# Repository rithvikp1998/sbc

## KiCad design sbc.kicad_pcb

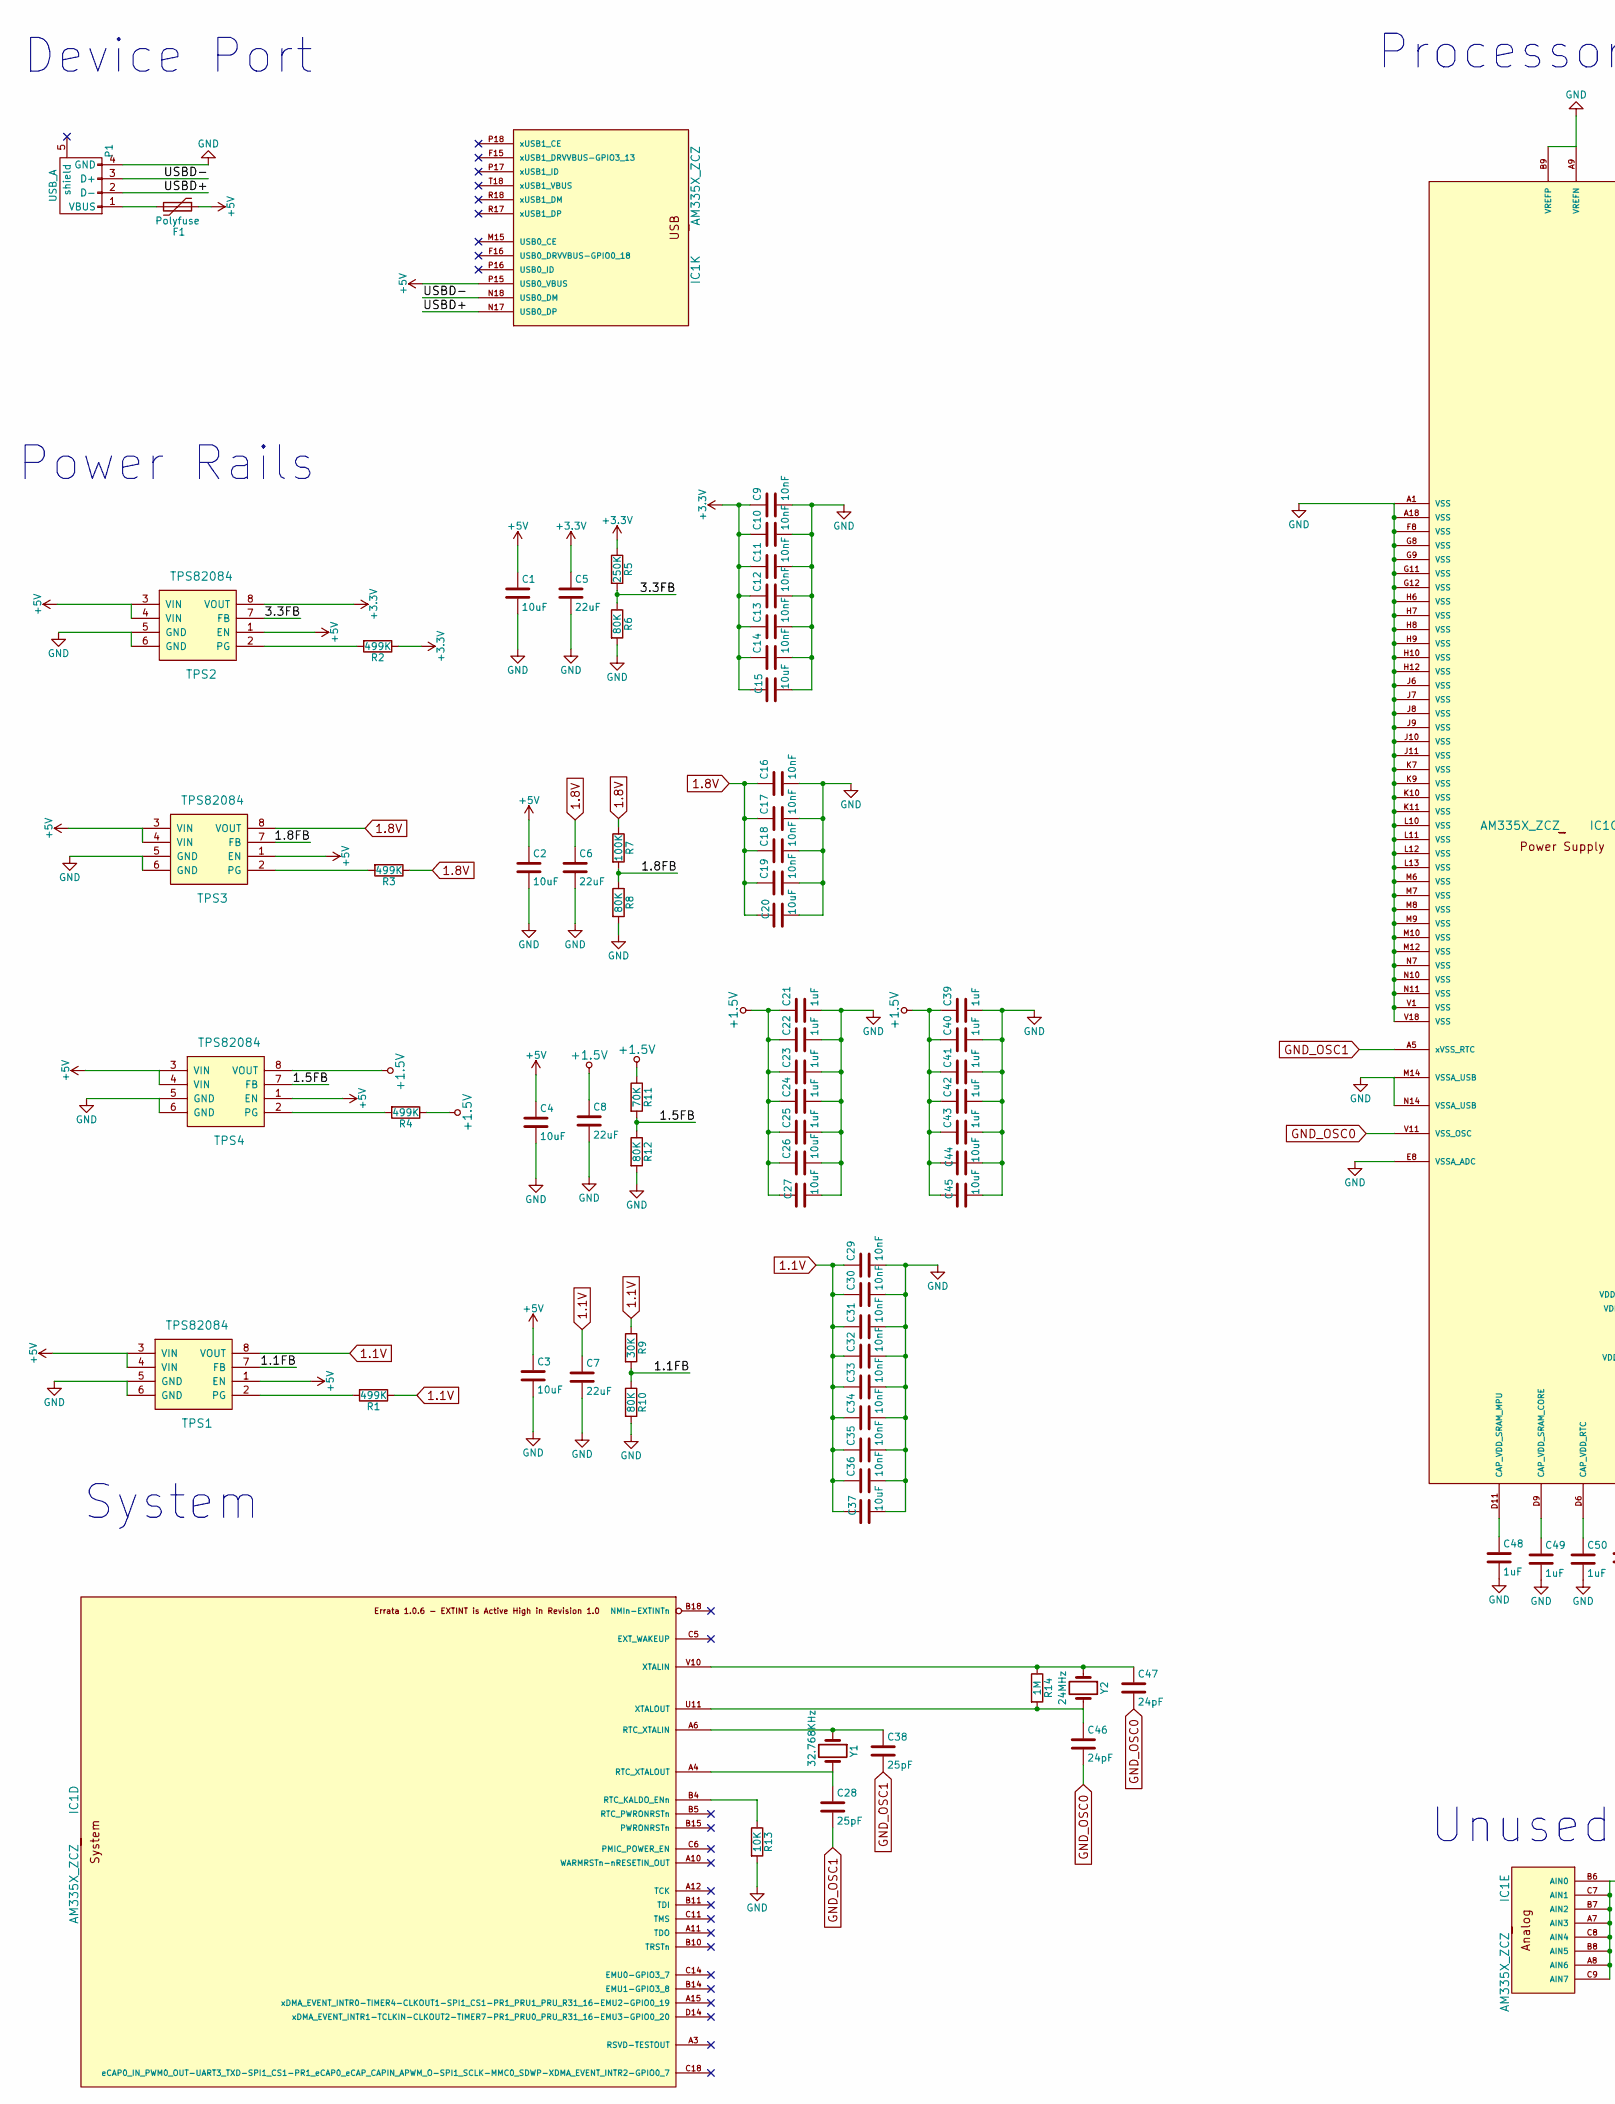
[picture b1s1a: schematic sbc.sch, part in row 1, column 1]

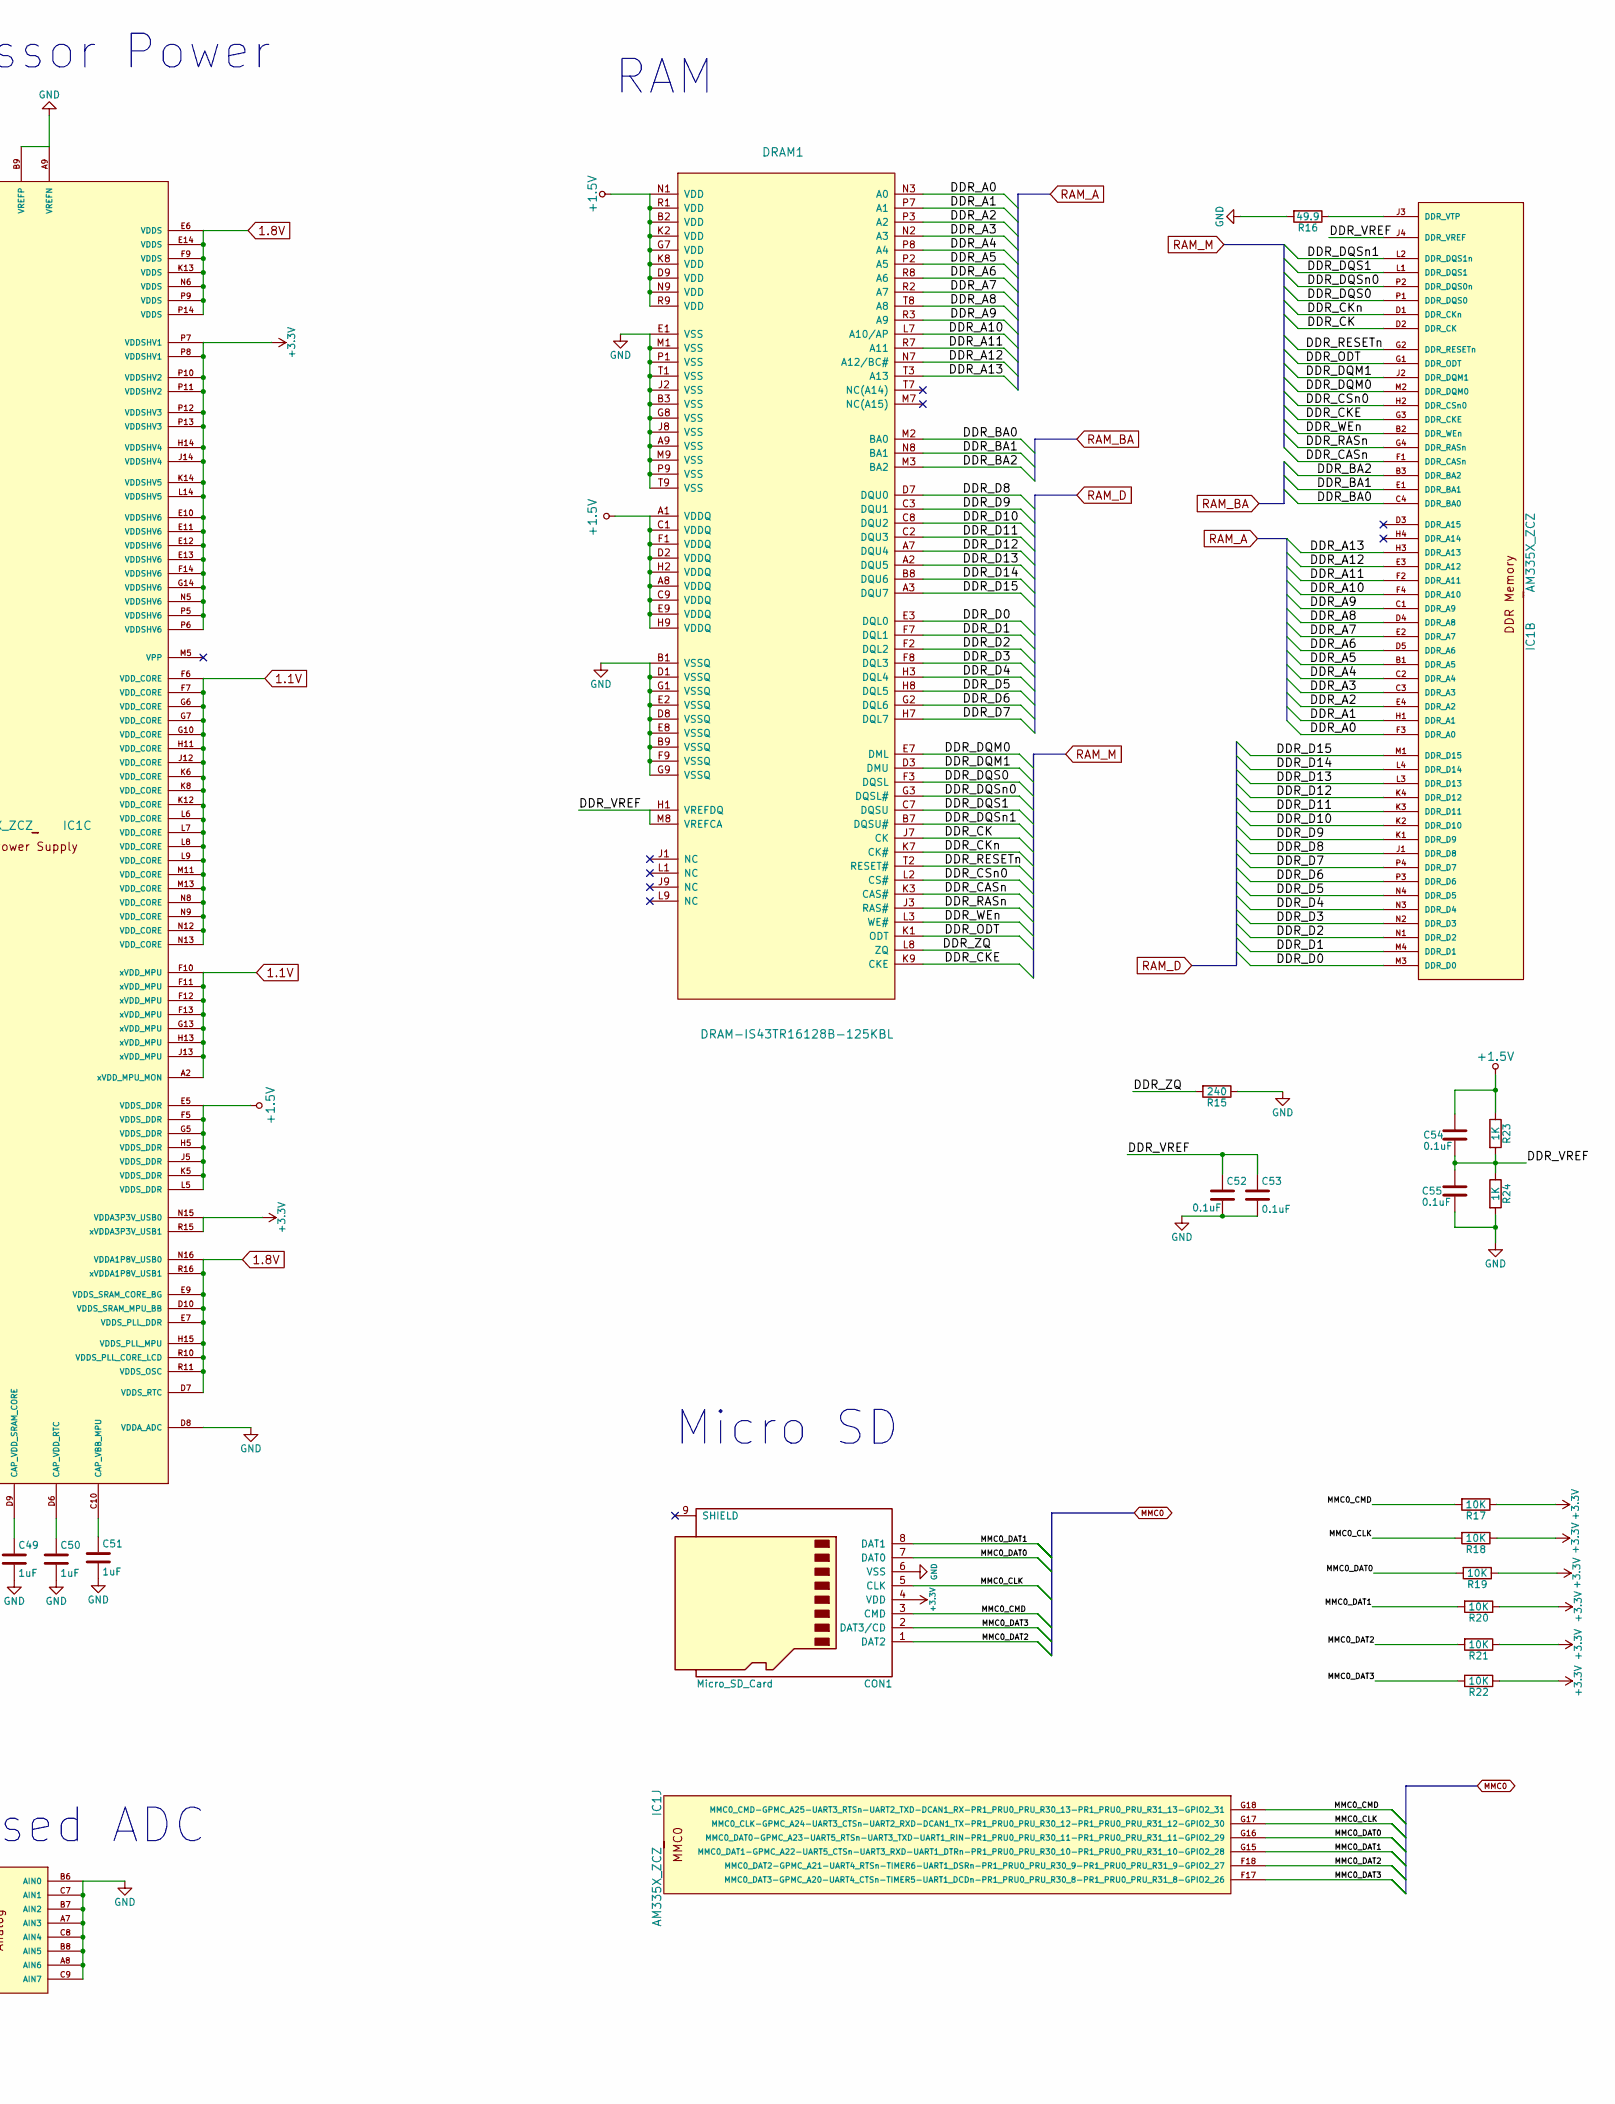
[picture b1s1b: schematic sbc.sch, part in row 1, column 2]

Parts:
C1, C2, C3, C4, C15, C20, C26, C27, C37, C44, C45: 10uF; C_0603_HandSoldering
C5, C6, C7, C8: 22uF; C_0603_HandSoldering
C9, C10, C11, C12, C13, C14, C16, C17, C18, C19, C29, C30, C31, C32, C33, C34, C35, C36: 10nF; C_0603_HandSoldering
C21, C22, C23, C24, C25, C39, C40, C41, C42, C43, C48, C49, C50, C51: 1uF; C_0603_HandSoldering
C28, C38: 25pF; C_0603_HandSoldering
C46, C47: 24pF; C_0603_HandSoldering
C52, C53, C54, C55: 0.1uF; C_0603_HandSoldering
CON1: Micro_SD_Card; MICRO_SD_HINGE_AMP
DRAM1: DRAM-IS43TR16128B-125KBL; BGA-96_pitch0.8mm_dia0.4mm
F1: Polyfuse; Fuse_SMD1206_HandSoldering
IC1: AM335X_ZCZ; bga-csg324
P1: USB_A
R1, R2, R3, R4: 499K; R_0603_HandSoldering
R5: 250K; R_0603_HandSoldering
R6, R8, R10, R12: 80K; R_0603_HandSoldering
R7: 100K; R_0603_HandSoldering
R9: 30K; R_0603_HandSoldering
R11: 70K; R_0603_HandSoldering
R13, R17, R18, R19, R20, R21, R22: 10K; R_0603_HandSoldering
R14: 1M; R_0603_HandSoldering
R15: 240; R_0603_HandSoldering
R16: 49.9; R_0603_HandSoldering
R23, R24: 1K; R_0603_HandSoldering
TPS1, TPS2, TPS3, TPS4: TPS82084; MSOP-8-1EP_3x3mm_Pitch0.65mm
Y1: 32.768KHz; Crystal_SMD_2012-2pin_2.0x1.2mm_HandSoldering
Y2: 24MHz; Crystal_SMD_2012-2pin_2.0x1.2mm_HandSoldering

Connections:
1.1V: C7.1, C29.1, C30.1, C31.1, C32.1, C33.1, C34.1, C35.1, C36.1, C37.2, IC1.A2 (xVDD_MPU_MON), IC1.F6 (VDD_CORE), IC1.F7 (VDD_CORE), IC1.F10 (xVDD_MPU), IC1.F11 (xVDD_MPU), IC1.F12 (xVDD_MPU), IC1.F13 (xVDD_MPU), IC1.G6 (VDD_CORE), IC1.G7 (VDD_CORE), IC1.G10 (VDD_CORE), IC1.G13 (xVDD_MPU), IC1.H11 (VDD_CORE), IC1.H13 (xVDD_MPU), IC1.J12 (VDD_CORE), IC1.J13 (xVDD_MPU), IC1.K6 (VDD_CORE), IC1.K8 (VDD_CORE), IC1.K12 (VDD_CORE), IC1.L6 (VDD_CORE), IC1.L7 (VDD_CORE), IC1.L8 (VDD_CORE), IC1.L9 (VDD_CORE), IC1.M11 (VDD_CORE), IC1.M13 (VDD_CORE), IC1.N8 (VDD_CORE), IC1.N9 (VDD_CORE), IC1.N12 (VDD_CORE), IC1.N13 (VDD_CORE), R1.1, R9.1, TPS1.8 (VOUT)
1.8V: C6.1, C16.1, C17.1, C18.1, C19.1, C20.2, IC1.D7 (VDDS_RTC), IC1.D10 (VDDS_SRAM_MPU_BB), IC1.E6 (VDDS), IC1.E7 (VDDS_PLL_DDR), IC1.E9 (VDDS_SRAM_CORE_BG), IC1.E14 (VDDS), IC1.F9 (VDDS), IC1.H15 (VDDS_PLL_MPU), IC1.K13 (VDDS), IC1.N6 (VDDS), IC1.N16 (VDDA1P8V_USB0), IC1.P9 (VDDS), IC1.P14 (VDDS), IC1.R10 (VDDS_PLL_CORE_LCD), IC1.R11 (VDDS_OSC), IC1.R16 (xVDDA1P8V_USB1), R3.1, R7.1, TPS3.8 (VOUT)
+1.5V: C8.1, C21.1, C22.1, C23.1, C24.1, C25.1, C26.1, C27.2, C39.1, C40.1, C41.1, C42.1, C43.1, C44.2, C45.2, C54.1, DRAM1.A1 (VDDQ), DRAM1.A8 (VDDQ), DRAM1.B2 (VDD), DRAM1.C1 (VDDQ), DRAM1.C9 (VDDQ), DRAM1.D2 (VDDQ), DRAM1.D9 (VDD), DRAM1.E9 (VDDQ), DRAM1.F1 (VDDQ), DRAM1.G7 (VDD), DRAM1.H2 (VDDQ), DRAM1.H9 (VDDQ), DRAM1.K2 (VDD), DRAM1.K8 (VDD), DRAM1.N1 (VDD), DRAM1.N9 (VDD), DRAM1.R1 (VDD), DRAM1.R9 (VDD), IC1.E5 (VDDS_DDR), IC1.F5 (VDDS_DDR), IC1.G5 (VDDS_DDR), IC1.H5 (VDDS_DDR), IC1.J5 (VDDS_DDR), IC1.K5 (VDDS_DDR), IC1.L5 (VDDS_DDR), R4.1, R11.1, R23.1, TPS4.8 (VOUT)
+3V3: C5.1, C9.1, C10.1, C11.1, C12.1, C13.1, C14.1, C15.2, CON1.4 (VDD), IC1.E10 (VDDSHV6), IC1.E11 (VDDSHV6), IC1.E12 (VDDSHV6), IC1.E13 (VDDSHV6), IC1.F14 (VDDSHV6), IC1.G14 (VDDSHV6), IC1.H14 (VDDSHV4), IC1.J14 (VDDSHV4), IC1.K14 (VDDSHV5), IC1.L14 (VDDSHV5), IC1.N5 (VDDSHV6), IC1.N15 (VDDA3P3V_USB0), IC1.P5 (VDDSHV6), IC1.P6 (VDDSHV6), IC1.P7 (VDDSHV1), IC1.P8 (VDDSHV1), IC1.P10 (VDDSHV2), IC1.P11 (VDDSHV2), IC1.P12 (VDDSHV3), IC1.P13 (VDDSHV3), IC1.R15 (xVDDA3P3V_USB1), R2.1, R5.1, R17.1, R18.1, R19.1, R20.1, R21.1, R22.1, TPS2.8 (VOUT)
+5V: C1.1, C2.1, C3.1, C4.1, F1.1, IC1.P15 (USB0_VBUS), TPS1.1 (EN), TPS1.3 (VIN), TPS1.4 (VIN), TPS2.1 (EN), TPS2.3 (VIN), TPS2.4 (VIN), TPS3.1 (EN), TPS3.3 (VIN), TPS3.4 (VIN), TPS4.1 (EN), TPS4.3 (VIN), TPS4.4 (VIN)
/1.1FB: R9.2, R10.1, TPS1.7 (FB)
/1.5FB: R11.2, R12.1, TPS4.7 (FB)
/1.8FB: R7.2, R8.1, TPS3.7 (FB)
/3.3FB: R5.2, R6.1, TPS2.7 (FB)
/DDR_A0: DRAM1.N3 (A0), IC1.F3 (DDR_A0)
/DDR_A1: DRAM1.P7 (A1), IC1.H1 (DDR_A1)
/DDR_A2: DRAM1.P3 (A2), IC1.E4 (DDR_A2)
/DDR_A3: DRAM1.N2 (A3), IC1.C3 (DDR_A3)
/DDR_A4: DRAM1.P8 (A4), IC1.C2 (DDR_A4)
/DDR_A5: DRAM1.P2 (A5), IC1.B1 (DDR_A5)
/DDR_A6: DRAM1.R8 (A6), IC1.D5 (DDR_A6)
/DDR_A7: DRAM1.R2 (A7), IC1.E2 (DDR_A7)
/DDR_A8: DRAM1.T8 (A8), IC1.D4 (DDR_A8)
/DDR_A9: DRAM1.R3 (A9), IC1.C1 (DDR_A9)
/DDR_A10: DRAM1.L7 (A10/AP), IC1.F4 (DDR_A10)
/DDR_A11: DRAM1.R7 (A11), IC1.F2 (DDR_A11)
/DDR_A12: DRAM1.N7 (A12/BC#), IC1.E3 (DDR_A12)
/DDR_A13: DRAM1.T3 (A13), IC1.H3 (DDR_A13)
/DDR_BA0: DRAM1.M2 (BA0), IC1.C4 (DDR_BA0)
/DDR_BA1: DRAM1.N8 (BA1), IC1.E1 (DDR_BA1)
/DDR_BA2: DRAM1.M3 (BA2), IC1.B3 (DDR_BA2)
/DDR_CASn: DRAM1.K3 (CAS#), IC1.F1 (DDR_CASn)
/DDR_CK: DRAM1.J7 (CK), IC1.D2 (DDR_CK)
/DDR_CKE: DRAM1.K9 (CKE), IC1.G3 (DDR_CKE)
/DDR_CKn: DRAM1.K7 (CK#), IC1.D1 (DDR_CKn)
/DDR_CSn0: DRAM1.L2 (CS#), IC1.H2 (DDR_CSn0)
/DDR_D0: DRAM1.E3 (DQL0), IC1.M3 (DDR_D0)
/DDR_D1: DRAM1.F7 (DQL1), IC1.M4 (DDR_D1)
/DDR_D2: DRAM1.F2 (DQL2), IC1.N1 (DDR_D2)
/DDR_D3: DRAM1.F8 (DQL3), IC1.N2 (DDR_D3)
/DDR_D4: DRAM1.H3 (DQL4), IC1.N3 (DDR_D4)
/DDR_D5: DRAM1.H8 (DQL5), IC1.N4 (DDR_D5)
/DDR_D6: DRAM1.G2 (DQL6), IC1.P3 (DDR_D6)
/DDR_D7: DRAM1.H7 (DQL7), IC1.P4 (DDR_D7)
/DDR_D8: DRAM1.D7 (DQU0), IC1.J1 (DDR_D8)
/DDR_D9: DRAM1.C3 (DQU1), IC1.K1 (DDR_D9)
/DDR_D10: DRAM1.C8 (DQU2), IC1.K2 (DDR_D10)
/DDR_D11: DRAM1.C2 (DQU3), IC1.K3 (DDR_D11)
/DDR_D12: DRAM1.A7 (DQU4), IC1.K4 (DDR_D12)
/DDR_D13: DRAM1.A2 (DQU5), IC1.L3 (DDR_D13)
/DDR_D14: DRAM1.B8 (DQU6), IC1.L4 (DDR_D14)
/DDR_D15: DRAM1.A3 (DQU7), IC1.M1 (DDR_D15)
/DDR_DQM0: DRAM1.E7 (DML), IC1.M2 (DDR_DQM0)
/DDR_DQM1: DRAM1.D3 (DMU), IC1.J2 (DDR_DQM1)
/DDR_DQS0: DRAM1.F3 (DQSL), IC1.P1 (DDR_DQS0)
/DDR_DQS1: DRAM1.C7 (DQSU), IC1.L1 (DDR_DQS1)
/DDR_DQSn0: DRAM1.G3 (DQSL#), IC1.P2 (DDR_DQS0n)
/DDR_DQSn1: DRAM1.B7 (DQSU#), IC1.L2 (DDR_DQS1n)
/DDR_ODT: DRAM1.K1 (ODT), IC1.G1 (DDR_ODT)
/DDR_RASn: DRAM1.J3 (RAS#), IC1.G4 (DDR_RASn)
/DDR_RESETn: DRAM1.T2 (RESET#), IC1.G2 (DDR_RESETn)
/DDR_VREF: C52.1, C53.1, C54.2, C55.1, DRAM1.H1 (VREFDQ), DRAM1.M8 (VREFCA), IC1.J4 (DDR_VREF), R23.2, R24.1
/DDR_WEn: DRAM1.L3 (WE#), IC1.B2 (DDR_WEn)
/DDR_ZQ: DRAM1.L8 (ZQ), R15.2
/MMC0_CLK: CON1.5 (CLK), IC1.G17 (MMC0_CLK-GPMC_A24-UART3_CTSn-UART2_RXD-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), R18.2
/MMC0_CMD: CON1.3 (CMD), IC1.G18 (MMC0_CMD-GPMC_A25-UART3_RTSn-UART2_TXD-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), R17.2
/MMC0_DAT0: CON1.7 (DAT0), IC1.G16 (MMC0_DAT0-GPMC_A23-UART5_RTSn-UART3_TXD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), R19.2
/MMC0_DAT1: CON1.8 (DAT1), IC1.G15 (MMC0_DAT1-GPMC_A22-UART5_CTSn-UART3_RXD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), R20.2
/MMC0_DAT2: CON1.1 (DAT2), IC1.F18 (MMC0_DAT2-GPMC_A21-UART4_RTSn-TIMER6-UA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), R21.2
/MMC0_DAT3: CON1.2 (DAT3/CD), IC1.F17 (MMC0_DAT3-GPMC_A20-UART4_CTSn-TIMER5-UA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), R22.2
/USBD+: IC1.N17 (USB0_DP), P1.2 (D-)
/USBD-: IC1.N18 (USB0_DM), P1.3 (D+)
GND: C1.2, C2.2, C3.2, C4.2, C5.2, C6.2, C7.2, C8.2, C9.2, C10.2, C11.2, C12.2, C13.2, C14.2, C15.1, C16.2, C17.2, C18.2, C19.2, C20.1, C21.2, C22.2, C23.2, C24.2, C25.2, C26.2, C27.1, C29.2, C30.2, C31.2, C32.2, C33.2, C34.2, C35.2, C36.2, C37.1, C39.2, C40.2, C41.2, C42.2, C43.2, C44.1, C45.1, C48.2, C49.2, C50.2, C51.2, C52.2, C53.2, C55.2, CON1.6 (VSS), DRAM1.A9 (VSS), DRAM1.B1 (VSSQ), DRAM1.B3 (VSS), DRAM1.B9 (VSSQ), DRAM1.D1 (VSSQ), DRAM1.D8 (VSSQ), DRAM1.E1 (VSS), DRAM1.E2 (VSSQ), DRAM1.E8 (VSSQ), DRAM1.F9 (VSSQ), DRAM1.G1 (VSSQ), DRAM1.G8 (VSS), DRAM1.G9 (VSSQ), DRAM1.J2 (VSS), DRAM1.J8 (VSS), DRAM1.M1 (VSS), DRAM1.M9 (VSS), DRAM1.P1 (VSS), DRAM1.P9 (VSS), DRAM1.T1 (VSS), DRAM1.T9 (VSS), IC1.A1 (VSS), IC1.A7 (AIN3), IC1.A8 (AIN6), IC1.A9 (VREFN), IC1.A18 (VSS), IC1.B6 (AIN0), IC1.B7 (AIN2), IC1.B8 (AIN5), IC1.B9 (VREFP), IC1.C7 (AIN1), IC1.C8 (AIN4), IC1.C9 (AIN7), IC1.D8 (VDDA_ADC), IC1.E8 (VSSA_ADC), IC1.F8 (VSS), IC1.G8 (VSS), IC1.G9 (VSS), IC1.G11 (VSS), IC1.G12 (VSS), IC1.H6 (VSS), IC1.H7 (VSS), IC1.H8 (VSS), IC1.H9 (VSS), IC1.H10 (VSS), IC1.H12 (VSS), IC1.J6 (VSS), IC1.J7 (VSS), IC1.J8 (VSS), IC1.J9 (VSS), IC1.J10 (VSS), IC1.J11 (VSS), IC1.K7 (VSS), IC1.K9 (VSS), IC1.K10 (VSS), IC1.K11 (VSS), IC1.L10 (VSS), IC1.L11 (VSS), IC1.L12 (VSS), IC1.L13 (VSS), IC1.M6 (VSS), IC1.M7 (VSS), IC1.M8 (VSS), IC1.M9 (VSS), IC1.M10 (VSS), IC1.M12 (VSS), IC1.M14 (VSSA_USB), IC1.N7 (VSS), IC1.N10 (VSS), IC1.N11 (VSS), IC1.N14 (VSSA_USB), IC1.V1 (VSS), IC1.V18 (VSS), P1.4 (GND), R6.2, R8.2, R10.2, R12.2, R13.2, R15.1, R16.2, R24.2, TPS1.5 (GND), TPS1.6 (GND), TPS2.5 (GND), TPS2.6 (GND), TPS3.5 (GND), TPS3.6 (GND), TPS4.5 (GND), TPS4.6 (GND)
GND_OSC0: C46.2, C47.2, IC1.V11 (VSS_OSC)
GND_OSC1: C28.2, C38.2, IC1.A5 (xVSS_RTC)
unnamed: C28.1, IC1.A4 (RTC_XTALOUT), Y1.2
unnamed: C38.1, IC1.A6 (RTC_XTALIN), Y1.1
unnamed: C46.1, IC1.U11 (XTALOUT), R14.2, Y2.2
unnamed: C47.1, IC1.V10 (XTALIN), R14.1, Y2.1
unnamed: C48.1, IC1.D11 (CAP_VDD_SRAM_MPU)
unnamed: C49.1, IC1.D9 (CAP_VDD_SRAM_CORE)
unnamed: C50.1, IC1.D6 (CAP_VDD_RTC)
unnamed: C51.1, IC1.C10 (CAP_VBB_MPU)
unnamed: F1.2, P1.1 (VBUS)
unnamed: IC1.B4 (RTC_KALDO_ENn), R13.1
unnamed: IC1.J3 (DDR_VTP), R16.1
unnamed: R1.2, TPS1.2 (PG)
unnamed: R2.2, TPS2.2 (PG)
unnamed: R3.2, TPS3.2 (PG)
unnamed: R4.2, TPS4.2 (PG)

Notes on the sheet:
Micro SD
RAM
Device Port
Processor Power
Power Rails
System
Unused ADC

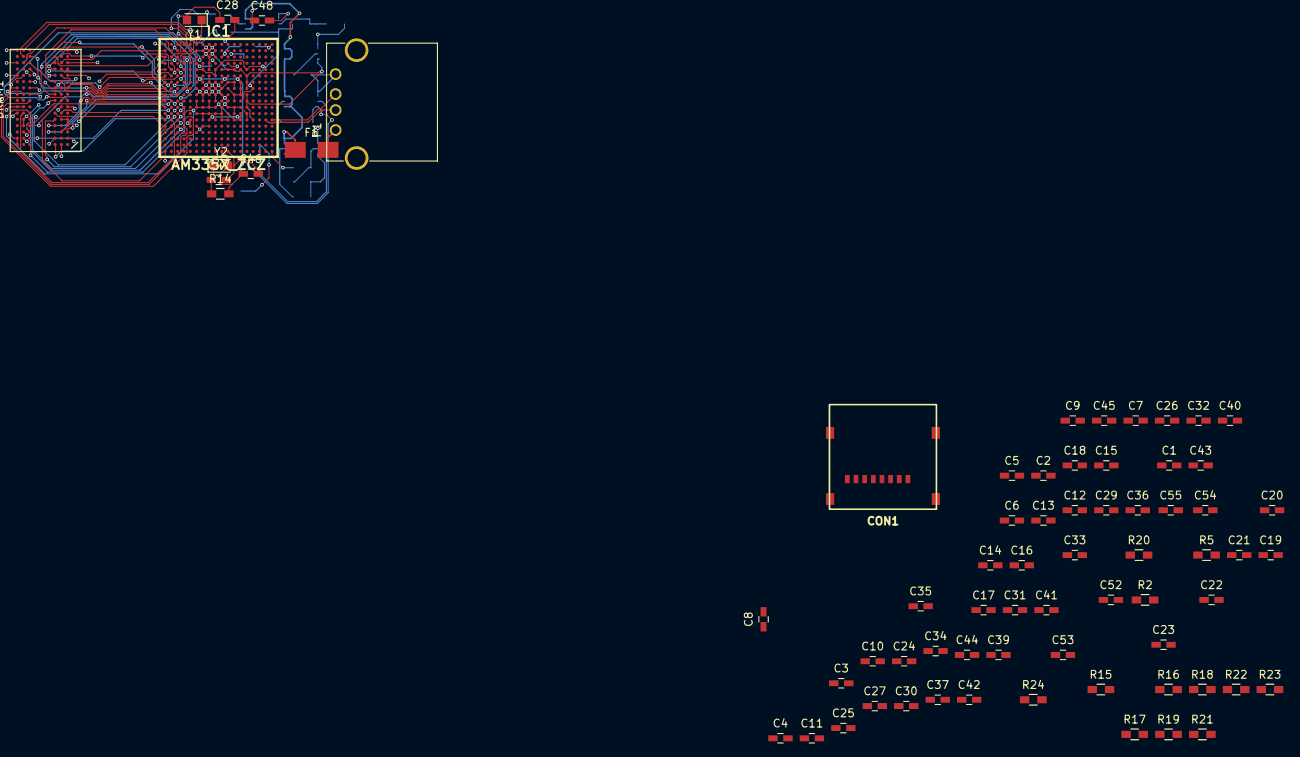
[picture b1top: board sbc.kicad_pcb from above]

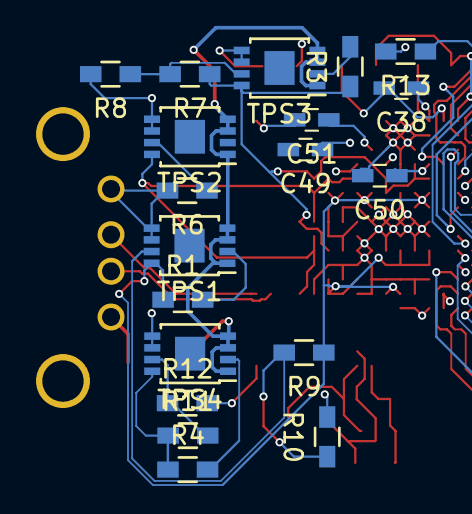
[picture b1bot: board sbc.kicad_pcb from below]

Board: 4 copper layers, 90 parts (19 on the bottom side), 85 nets.

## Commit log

2017-01-18 Made a schematic symbol for RAM
2017-01-20 Added buck converter to library
2017-01-20 Connected micro SD
2017-01-22 Connected RAM
2017-01-23 Added Power, USB, System
2017-01-23 Schematic completed
2017-01-23 Fixed errors
2017-01-26 Regualar backup commit
2017-01-27 Regular backup
2017-01-28 board design v1 almost complete
